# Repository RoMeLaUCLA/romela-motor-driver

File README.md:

# RoMeLa motor driver gen2
 Motor driver PCB and firmware designed for RoMeLa actuators. 
 
 Block diagram of the hardware:

 ## System Diagram

 # PCB reference

[Link to gen2 schematics](/pcb/rev1/schematics_Motor_Gen2.pdf)

[Link to gen2L schematics](/pcb/split/gen2L/schematics_Motor_Gen2L.pdf)

[Link to gen2P schematics](/pcb/split/gen2P/schematics_Motor_Gen2P.pdf)

# Change Log
12/1/2022 Ver. 581
- First version using gcc(STM32CubeIDE)

04/13/2022 Ver. 48D
- Added 0.5ms de-glitch time for E-Stop input and 1sec minimum E-Stop time.

02/09/2022 Ver. 449
- Fixed MCU lock up with RS-485 over run present in Ver. 2BB.

09/27/2021 Ver. 33B
- Random ABS Posi error and Init error on power-up.

05/27/2021 Ver. 2BB
- Fixed cogging torque comp. issue.

03/31/2021 Ver. 27F
- Limit Id Max changed to Limit Acc Max
- Limit Iq Max changed to Limit I Max
- Added external Estop signal (wiring change) and command
- Acceleration limited S curve added to Mode 2 (position mode).
- Goal velocity and Iq feedforward term enabled for Mode 3. (Allow Id, Iq, Velocity, Position reference all at once)

09/29/2020 Ver. 130-137
- Added support for KB01_R18 and KB01_R24. (External AS5047 Encoder)

06/23/2020 Ver. D7
- Fixed joint limit issue.

05/20/2020 Ver. B4
- GEN2 Initial release.

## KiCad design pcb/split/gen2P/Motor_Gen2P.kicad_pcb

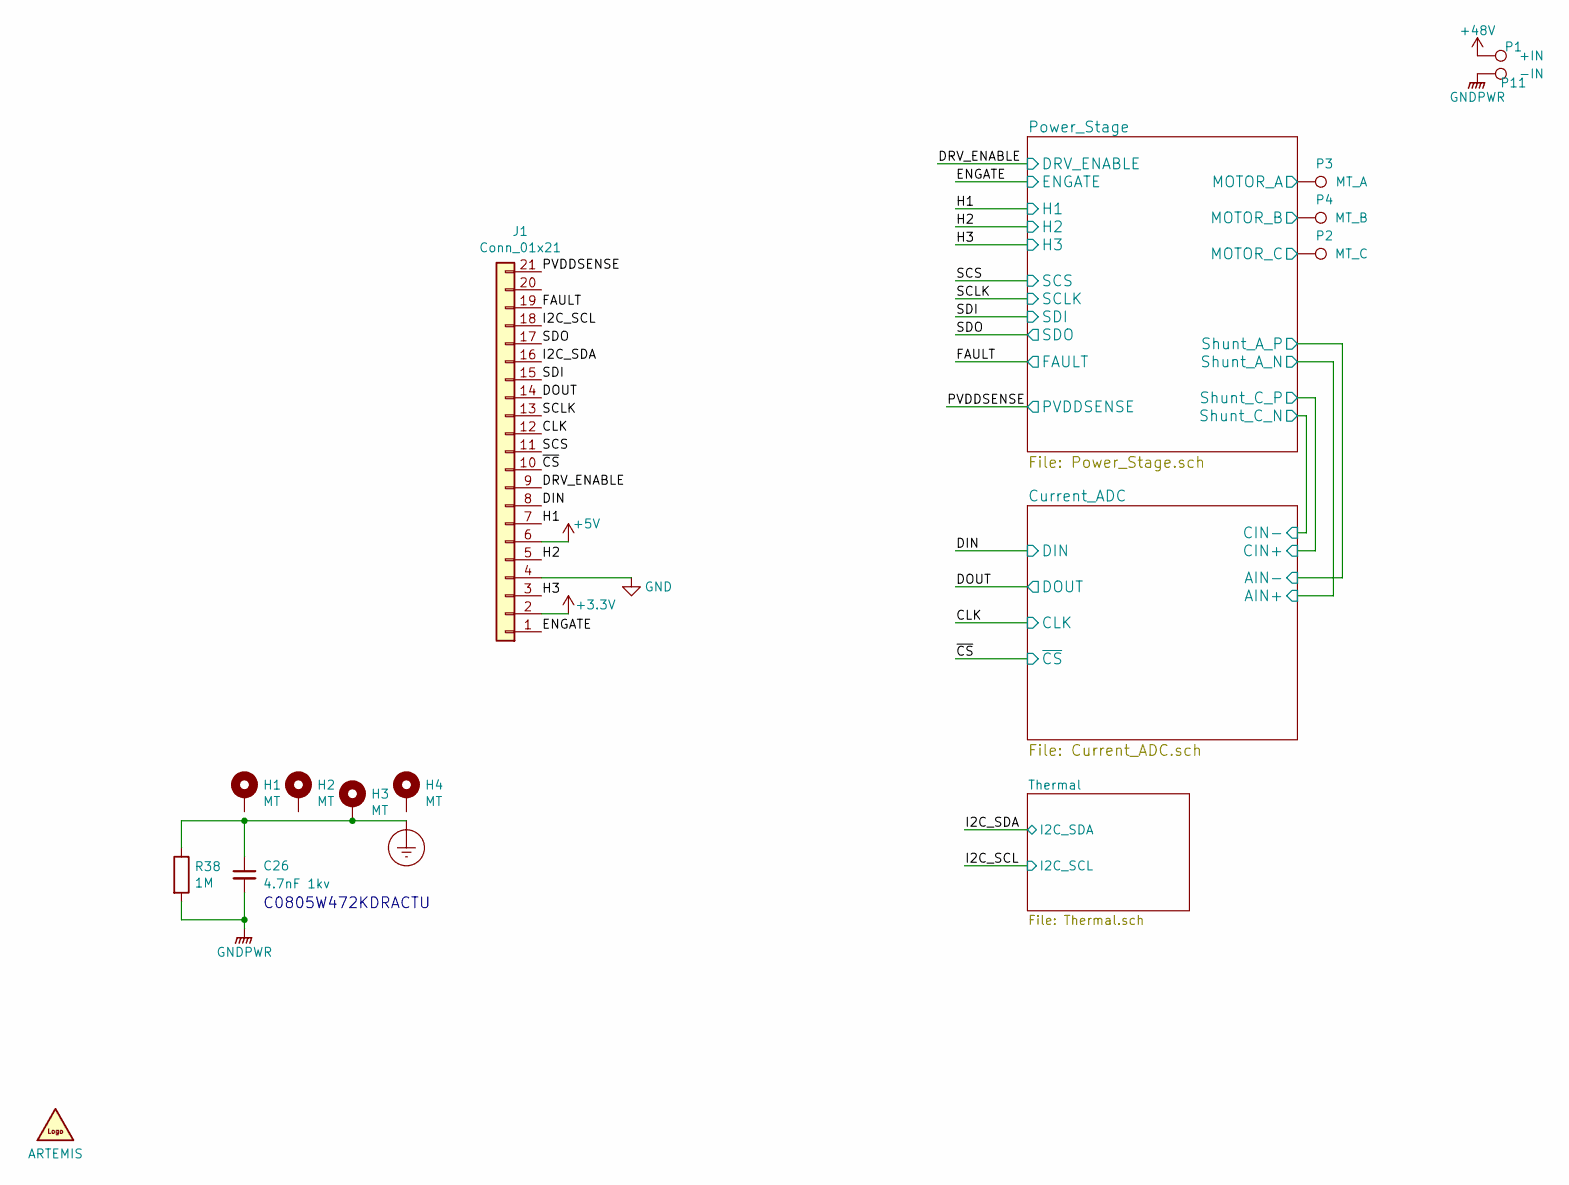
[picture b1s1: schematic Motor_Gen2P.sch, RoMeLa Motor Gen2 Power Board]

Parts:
C26: 4.7nF 1kv; C_0805_2012Metric
G1: ARTEMIS; artemis_logo_small
H1, H2, H3, H4: MT; MountingHole_2.7mm_M2.5_Pad_Via
J1: Conn_01x21; Molex_5019122190_2Rows-21Pins_P0.30mm
P1: +IN; Motor_winding_SMT
P2: MT_C; motor_winding_oval_3mm
P3: MT_A; motor_winding_oval_3mm
P4: MT_B; motor_winding_oval_3mm
P11: -IN; Motor_winding_SMT
R38: 1M; R_0805_2012Metric

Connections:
+3V3: J1.2; also elsewhere on the board
+5V: J1.6; also elsewhere on the board
+48V: P1.1; also elsewhere on the board
/CLK: J1.12; also elsewhere on the board
/DIN: J1.8; also elsewhere on the board
/DOUT: J1.14; also elsewhere on the board
/DRV_ENABLE: J1.9; also elsewhere on the board
/ENGATE: J1.1; also elsewhere on the board
/FAULT: J1.19; also elsewhere on the board
/H1: J1.7; also elsewhere on the board
/H2: J1.5; also elsewhere on the board
/H3: J1.3; also elsewhere on the board
/I2C_SCL: J1.18; also elsewhere on the board
/I2C_SDA: J1.16; also elsewhere on the board
/PVDDSENSE: J1.21; also elsewhere on the board
/Power_Stage/MOTOR_A: P3.1; also elsewhere on the board
/Power_Stage/MOTOR_B: P4.1; also elsewhere on the board
/Power_Stage/MOTOR_C: P2.1; also elsewhere on the board
/SCLK: J1.13; also elsewhere on the board
/SCS: J1.11; also elsewhere on the board
/SDI: J1.15; also elsewhere on the board
/SDO: J1.17; also elsewhere on the board
/~CS: J1.10; also elsewhere on the board
Earth_Protective: C26.1, H3.1, R38.1
GND: J1.4; also elsewhere on the board
GNDPWR: C26.2, P11.1, R38.2; also elsewhere on the board

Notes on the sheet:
C0805W472KDRACTU

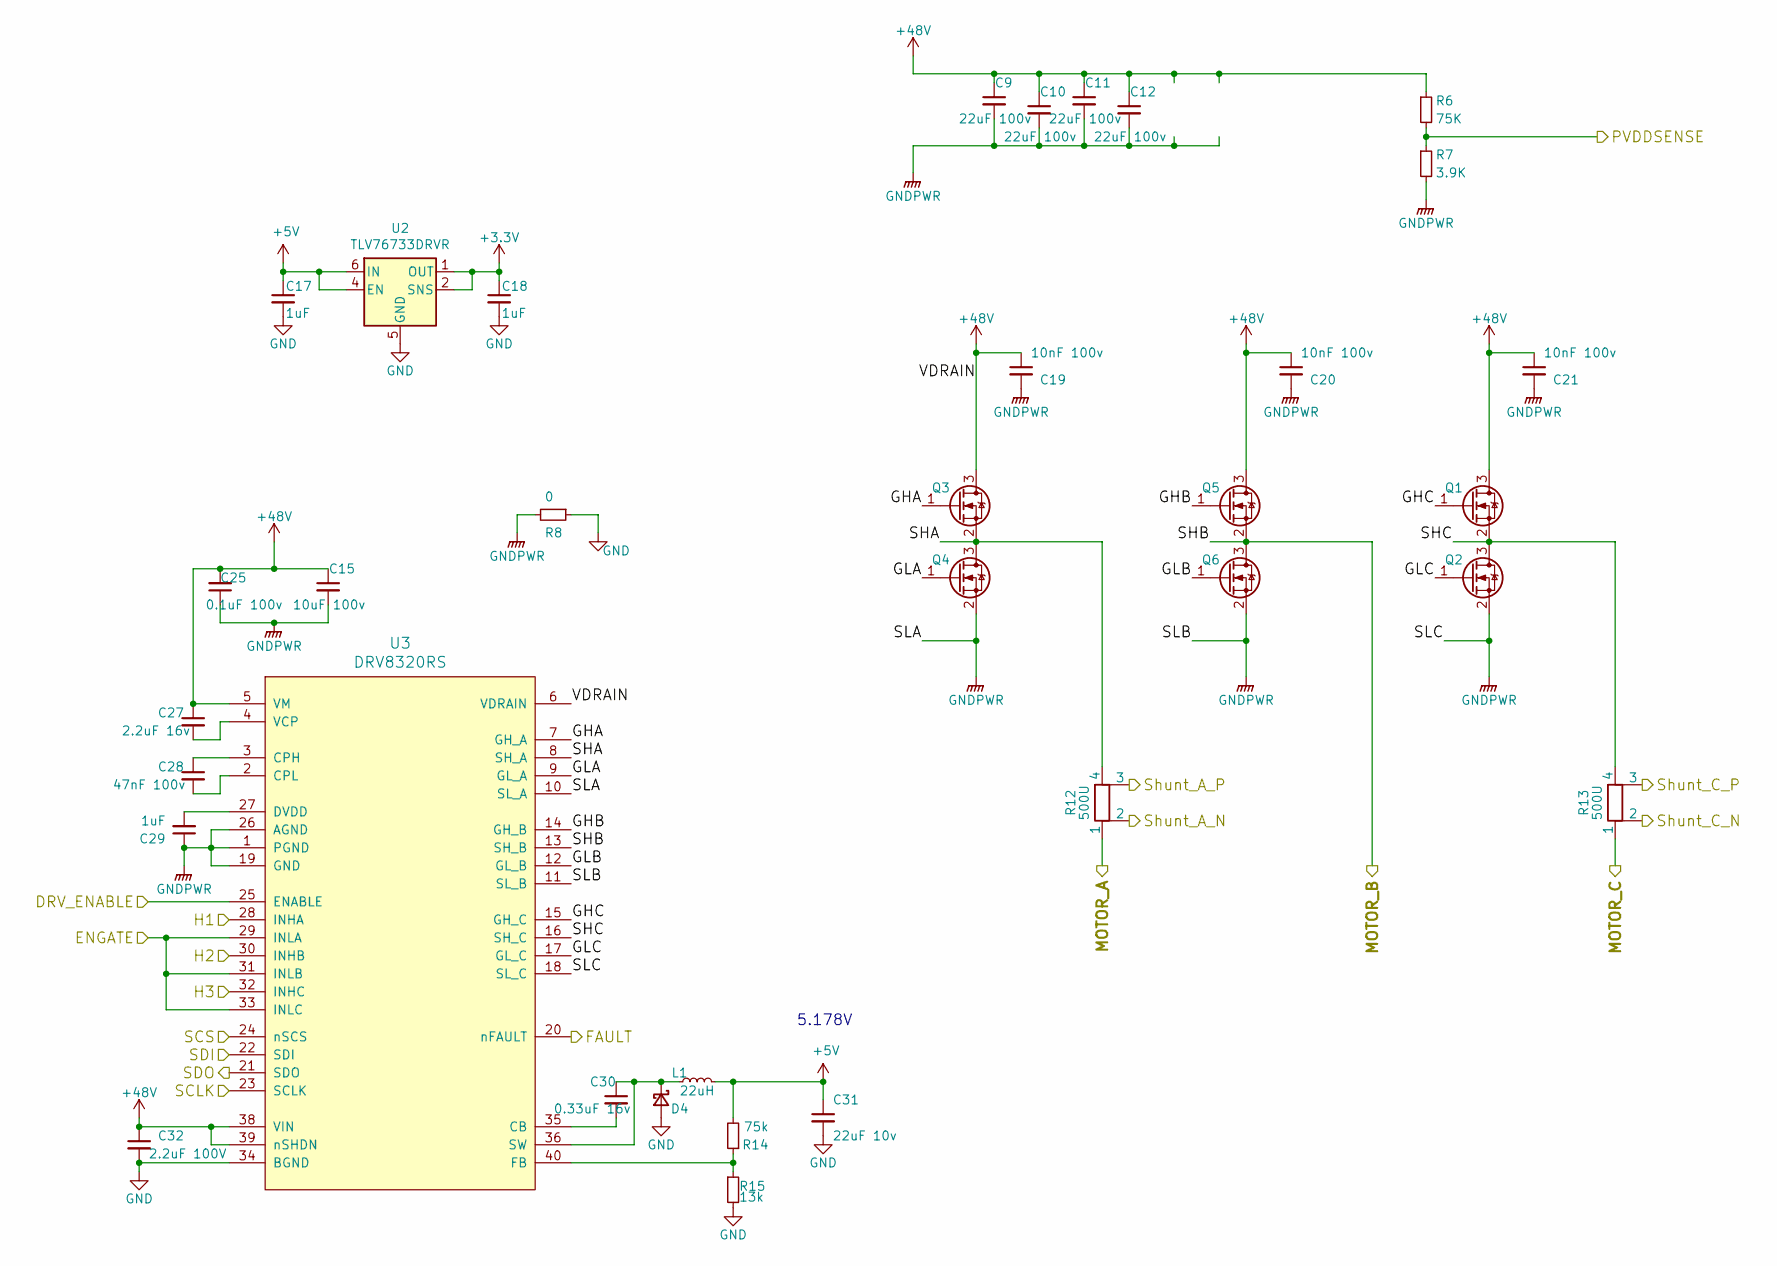
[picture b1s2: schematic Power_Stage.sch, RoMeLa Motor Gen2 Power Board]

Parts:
C9, C10, C11, C12: 22uF 100v; C_2220_5650Metric
C15: 10uF 100v; C_1210_3225Metric
C17, C18, C29: 1uF; C_0603_1608Metric
C19, C20, C21: 10nF 100v; C_0603_1608Metric
C25: 0.1uF 100v; C_0603_1608Metric
C27: 2.2uF 16v; C_0603_1608Metric
C28: 47nF 100v; C_0603_1608Metric
C30: 0.33uF 16v; C_0603_1608Metric
C31: 22uF 10v; C_1206_3216Metric
C32: 2.2uF 100V; C_1206_3216Metric
D4: D_Schottky_Small; D_TUMD2
L1: 22uH; L_Taiyo-Yuden_DND4040WK
Q1, Q2, Q3, Q4, Q5, Q6: NMOS; DFNW8_8.3x8.4_short
R6: 75K; R_0402_1005Metric
R7: 3.9K; R_0402_1005Metric
R8: 0; NetTie-2_SMD_Pad0.5mm
R12, R13: 500U; RES_W1612_4Terminal
R14: 75k; R_0402_1005Metric
R15: 13k; R_0402_1005Metric
U2: TLV76733DRVR; WSON-6-1EP_2x2mm_P0.65mm_EP1x1.6mm
U3: DRV8320RS; Texas_S-PVQFN-N40_EP4.15x4.15mm

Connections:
+3V3: C18.1, U2.1 (OUT), U2.2 (SNS); also elsewhere on the board
+5V: C17.1, C31.1, L1.2, R14.2, U2.4 (EN), U2.6 (IN); also elsewhere on the board
+48V: C9.1, C10.1, C11.1, C12.1, C15.1, C19.1, C20.1, C21.1, C25.2, C27.1, C32.1, Q1.3 (D), Q3.3 (D), Q5.3 (D), R6.1, U3.5 (VM), U3.6 (VDRAIN), U3.38 (VIN), U3.39 (nSHDN); also elsewhere on the board
/Current_ADC/AIN+: R12.2; also elsewhere on the board
/Current_ADC/AIN-: R12.3; also elsewhere on the board
/Current_ADC/CIN+: R13.3; also elsewhere on the board
/Current_ADC/CIN-: R13.2; also elsewhere on the board
/DRV_ENABLE: U3.25 (ENABLE); also elsewhere on the board
/ENGATE: U3.29 (INLA), U3.31 (INLB), U3.33 (INLC); also elsewhere on the board
/FAULT: U3.20 (nFAULT); also elsewhere on the board
/H1: U3.28 (INHA); also elsewhere on the board
/H2: U3.30 (INHB); also elsewhere on the board
/H3: U3.32 (INHC); also elsewhere on the board
/PVDDSENSE: R6.2, R7.1; also elsewhere on the board
/Power_Stage/GHA: Q3.1 (G), U3.7 (GH_A)
/Power_Stage/GHB: Q5.1 (G), U3.14 (GH_B)
/Power_Stage/GHC: Q1.1 (G), U3.15 (GH_C)
/Power_Stage/GLA: Q4.1 (G), U3.9 (GL_A)
/Power_Stage/GLB: Q6.1 (G), U3.12 (GL_B)
/Power_Stage/GLC: Q2.1 (G), U3.17 (GL_C)
/Power_Stage/MOTOR_A: R12.1; also elsewhere on the board
/Power_Stage/MOTOR_B: Q5.2 (S), Q6.3 (D), U3.13 (SH_B); also elsewhere on the board
/Power_Stage/MOTOR_C: R13.1; also elsewhere on the board
/Power_Stage/SHA: Q3.2 (S), Q4.3 (D), R12.4, U3.8 (SH_A)
/Power_Stage/SHC: Q1.2 (S), Q2.3 (D), R13.4, U3.16 (SH_C)
/SCLK: U3.23 (SCLK); also elsewhere on the board
/SCS: U3.24 (nSCS); also elsewhere on the board
/SDI: U3.22 (SDI); also elsewhere on the board
/SDO: U3.21 (SDO); also elsewhere on the board
GND: C17.2, C18.2, C31.2, C32.2, D4.2 (A), R8.1, R15.2, U2.3 (GND), U2.5 (GND), U2.7 (GND), U3.34 (BGND); also elsewhere on the board
GNDPWR: C9.2, C10.2, C11.2, C12.2, C15.2, C19.2, C20.2, C21.2, C25.1, C29.1, Q2.2 (S), Q4.2 (S), Q6.2 (S), R7.2, R8.2, U3.1 (PGND), U3.10 (SL_A), U3.11 (SL_B), U3.18 (SL_C), U3.19 (GND), U3.26 (AGND), U3.41 (PAD); also elsewhere on the board
unnamed: C27.2, U3.4 (VCP)
unnamed: C28.1, U3.3 (CPH)
unnamed: C28.2, U3.2 (CPL)
unnamed: C29.2, U3.27 (DVDD)
unnamed: C30.1, D4.1 (K), L1.1, U3.36 (SW)
unnamed: C30.2, U3.35 (CB)
unnamed: R14.1, R15.1, U3.40 (FB)

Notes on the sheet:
5.178V

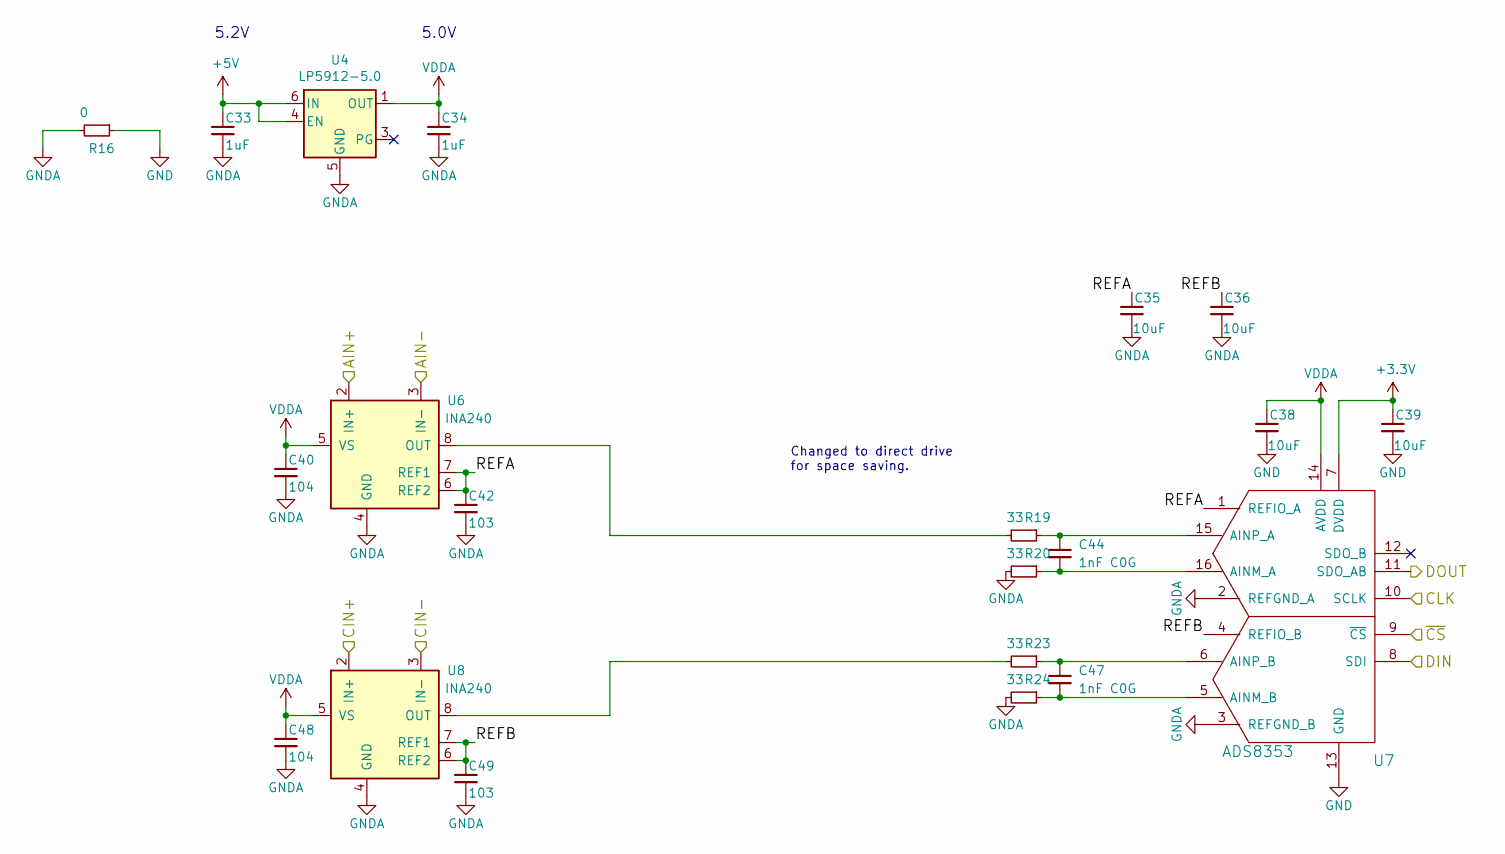
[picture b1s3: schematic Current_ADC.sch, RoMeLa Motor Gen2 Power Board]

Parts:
C33, C34: 1uF; C_0603_1608Metric
C35, C36, C38, C39: 10uF; C_0805_2012Metric
C40, C48: 104; C_0402_1005Metric
C42, C49: 103; C_0402_1005Metric
C44, C47: 1nF C0G; C_0402_1005Metric
R16: 0; NetTie-2_SMD_Pad0.5mm
R19, R20, R23, R24: 33; R_0402_1005Metric
U4: LP5912-5.0; WSON-6-1EP_2x2mm_P0.65mm_EP1x1.6mm
U6, U8: INA240; TSSOP-8_4.4x3mm_P0.65mm
U7: ADS8353; WQFN-16-1EP_3x3mm_P0.5mm_EP0.8x0.8mm

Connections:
+3V3: C39.1, U7.7 (DVDD); also elsewhere on the board
+5V: C33.1, U4.4 (EN), U4.6 (IN); also elsewhere on the board
/CLK: U7.10 (SCLK); also elsewhere on the board
/Current_ADC/AIN+: U6.2 (IN+); also elsewhere on the board
/Current_ADC/AIN-: U6.3 (IN-); also elsewhere on the board
/Current_ADC/CIN+: U8.2 (IN+); also elsewhere on the board
/Current_ADC/CIN-: U8.3 (IN-); also elsewhere on the board
/Current_ADC/REFA: C35.1, C42.1, U6.6 (REF2), U6.7 (REF1), U7.1 (REFIO_A)
/Current_ADC/REFB: C36.1, C49.1, U7.4 (REFIO_B), U8.6 (REF2), U8.7 (REF1)
/DIN: U7.8 (SDI); also elsewhere on the board
/DOUT: U7.11 (SDO_AB); also elsewhere on the board
/~CS: U7.9 (~CS); also elsewhere on the board
GND: C38.2, C39.2, R16.1, U7.13 (GND), U7.17 (Pad); also elsewhere on the board
GNDA: C33.2, C34.2, C35.2, C36.2, C40.2, C42.2, C48.2, C49.2, R16.2, R20.2, R24.2, U4.5 (GND), U4.7 (GND), U6.4 (GND), U7.2 (REFGND_A), U7.3 (REFGND_B), U8.4 (GND)
unnamed: C44.1, R19.1, U7.15 (AINP_A)
unnamed: C44.2, R20.1, U7.16 (AINM_A)
unnamed: C47.1, R23.1, U7.6 (AINP_B)
unnamed: C47.2, R24.1, U7.5 (AINM_B)
unnamed: R19.2, U6.8 (OUT)
unnamed: R23.2, U8.8 (OUT)
VDDA: C34.1, C38.1, C40.1, C48.1, U4.1 (OUT), U6.5 (VS), U7.14 (AVDD), U8.5 (VS)

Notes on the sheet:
5.2V
5.0V
Changed to direct drive for space saving.

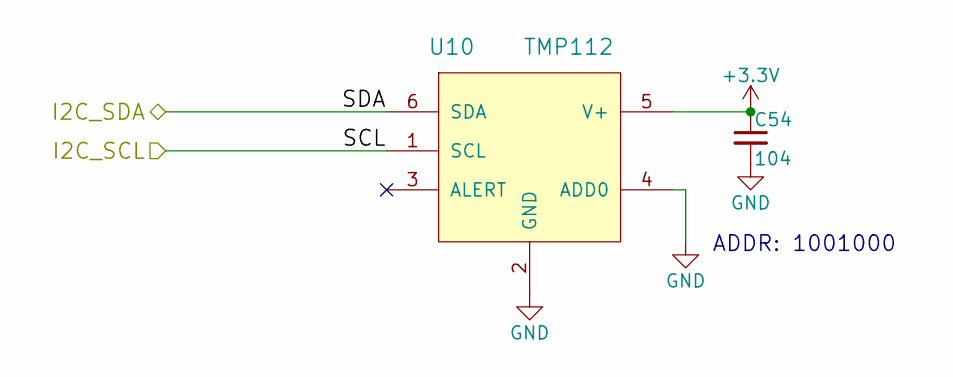
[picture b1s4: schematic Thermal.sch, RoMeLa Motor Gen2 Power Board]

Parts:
C54: 104; C_0402_1005Metric
U10: TMP112; SOT-563

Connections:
+3V3: C54.1, U10.5 (V+); also elsewhere on the board
/I2C_SCL: U10.1 (SCL); also elsewhere on the board
/I2C_SDA: U10.6 (SDA); also elsewhere on the board
GND: C54.2, U10.2 (GND), U10.4 (ADD0); also elsewhere on the board

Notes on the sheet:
ADDR: 1001000

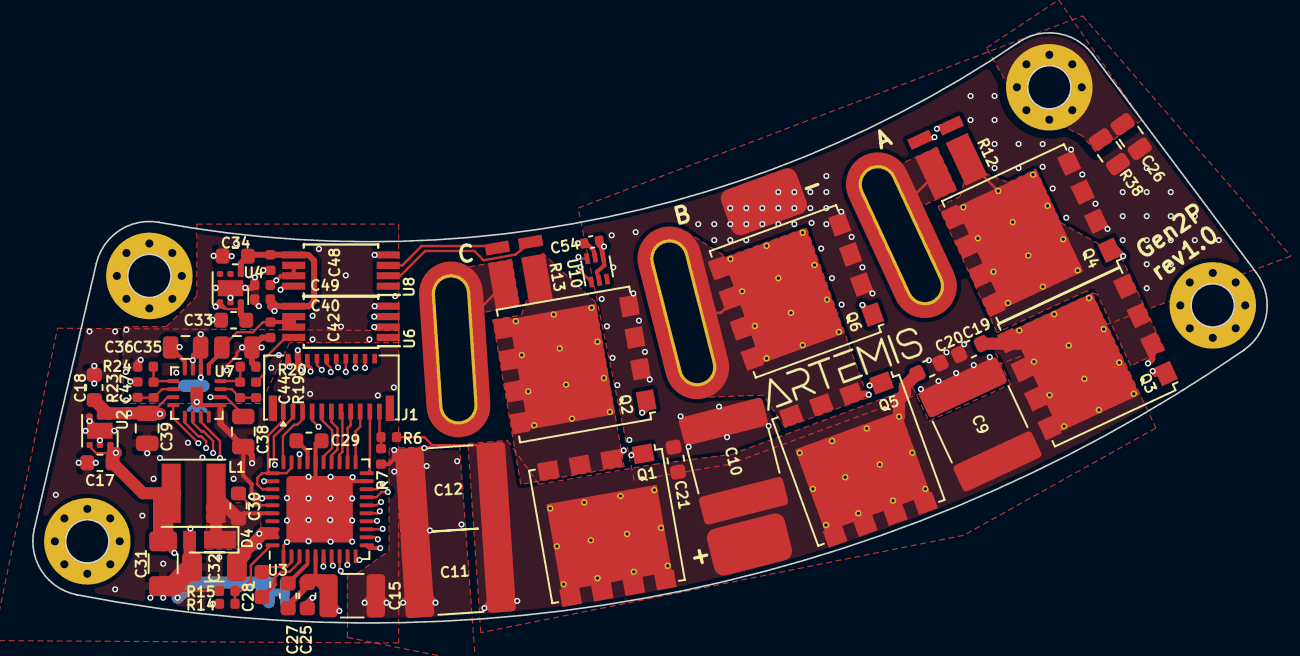
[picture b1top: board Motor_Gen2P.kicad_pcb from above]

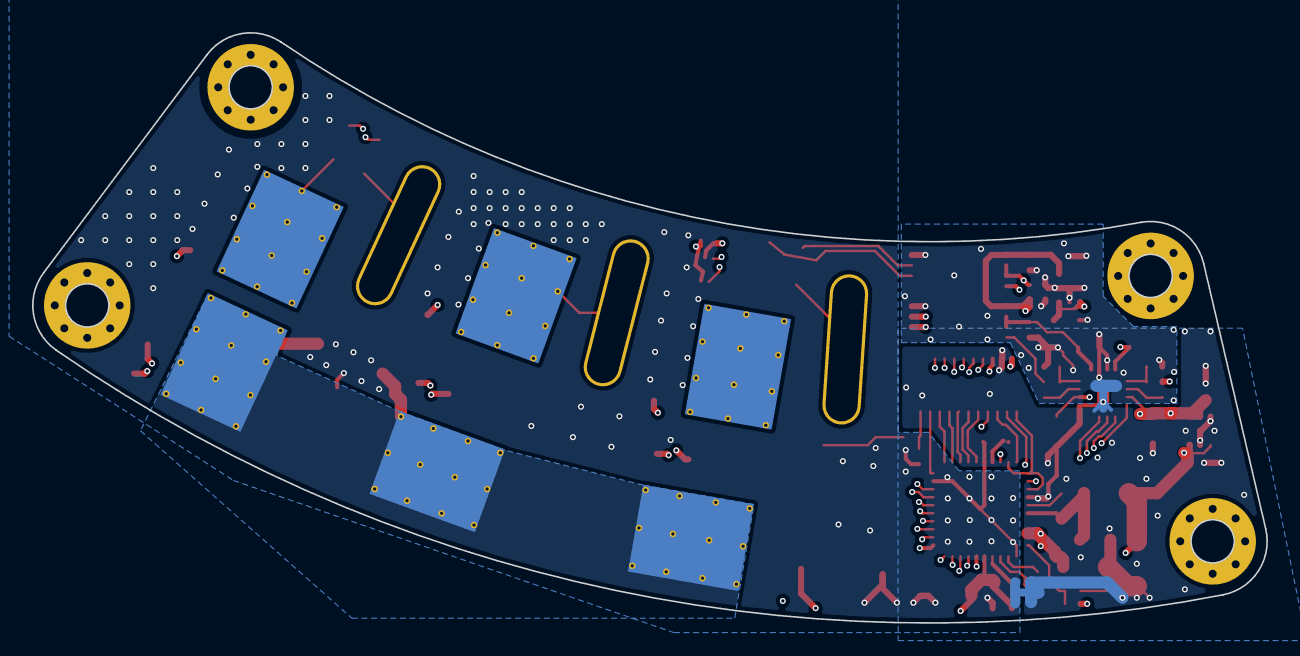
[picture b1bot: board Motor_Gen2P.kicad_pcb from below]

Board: 4 copper layers, 77.1 x 36.8 mm, 70 parts (2 on the bottom side), 55 nets.

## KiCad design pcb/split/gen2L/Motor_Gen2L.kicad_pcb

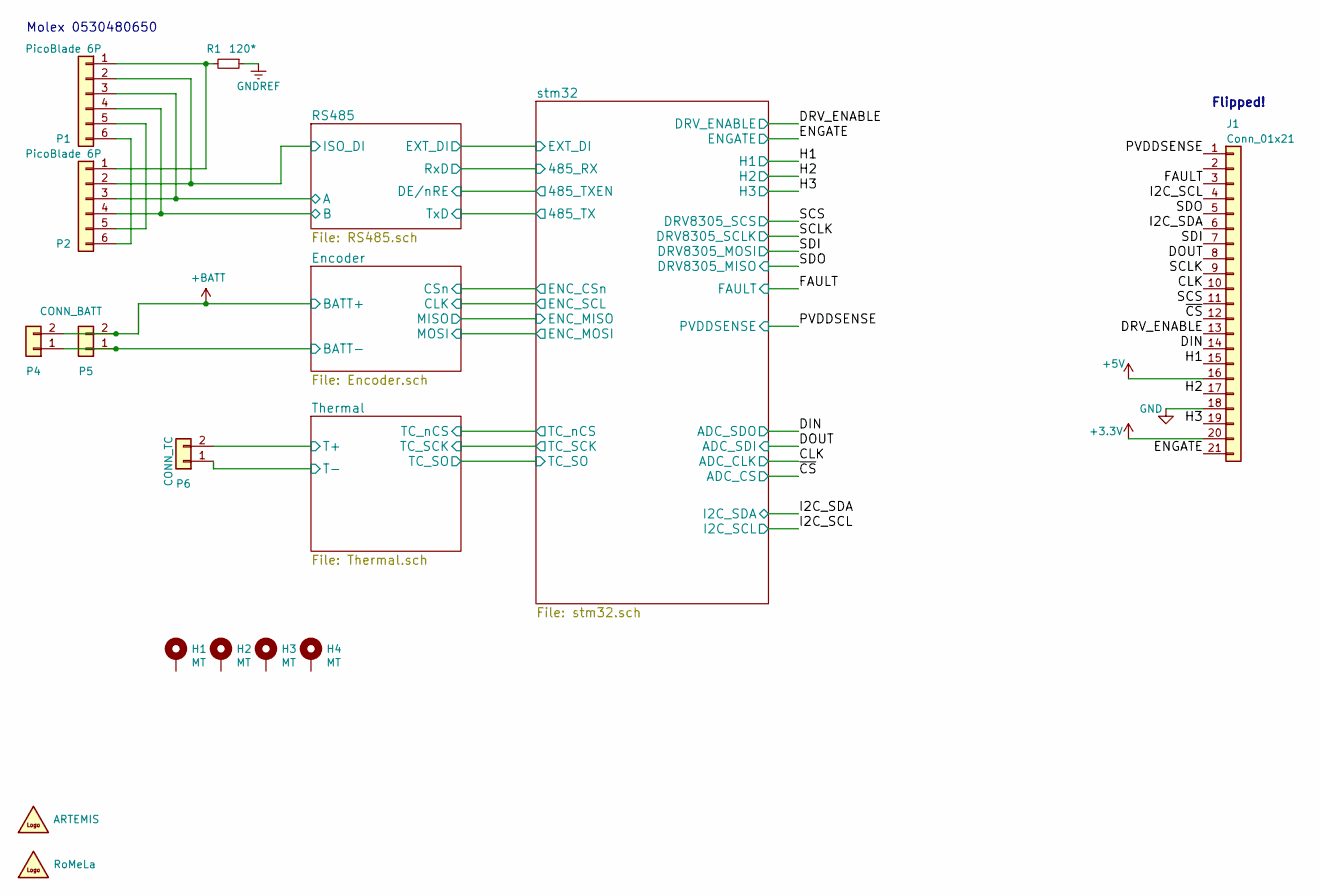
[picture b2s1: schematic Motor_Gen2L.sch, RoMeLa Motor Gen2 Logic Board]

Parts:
G1: ARTEMIS; artemis_logo_small
G2: RoMeLa; LOGO
H1, H2, H3, H4: MT; MountingHole_2.7mm_M2.5_Pad_Via
J1: Conn_01x21; Molex_5019122190_2Rows-21Pins_P0.30mm
P1, P2: PicoBlade 6P; Molex_PicoBlade_53048-0650_1x06_P1.25mm_Horizontal
P4, P5: CONN_BATT; Molex_PicoBlade_53048-0210_1x02_P1.25mm_Horizontal
P6: CONN_TC; JST_SH_SM02B-SRSS-TB_1x02-1MP_P1.00mm_Horizontal
R1: 120*; R_0603_1608Metric

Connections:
+3V3: J1.20; also elsewhere on the board
+5V: J1.16; also elsewhere on the board
+BATT: P4.2, P5.2; also elsewhere on the board
/CLK: J1.10; also elsewhere on the board
/DIN: J1.14; also elsewhere on the board
/DOUT: J1.8; also elsewhere on the board
/DRV_ENABLE: J1.13; also elsewhere on the board
/ENGATE: J1.21; also elsewhere on the board
/FAULT: J1.3; also elsewhere on the board
/H1: J1.15; also elsewhere on the board
/H2: J1.17; also elsewhere on the board
/H3: J1.19; also elsewhere on the board
/I2C_SCL: J1.4; also elsewhere on the board
/I2C_SDA: J1.6; also elsewhere on the board
/PVDDSENSE: J1.1; also elsewhere on the board
/RS485/A: P1.3, P2.3; also elsewhere on the board
/RS485/B: P1.4, P2.4; also elsewhere on the board
/RS485/ISO_DI: P1.2, P2.2; also elsewhere on the board
/SCLK: J1.9; also elsewhere on the board
/SCS: J1.11; also elsewhere on the board
/SDI: J1.7; also elsewhere on the board
/SDO: J1.5; also elsewhere on the board
/Thermal/T+: P6.2; also elsewhere on the board
/Thermal/T-: P6.1; also elsewhere on the board
/~CS: J1.12; also elsewhere on the board
GND: J1.18, P4.1, P5.1; also elsewhere on the board
GNDREF: R1.1; also elsewhere on the board
unnamed: P1.1, P2.1, R1.2
unnamed: P1.5, P2.5
unnamed: P1.6, P2.6

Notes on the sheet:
Molex 0530480650
Flipped!

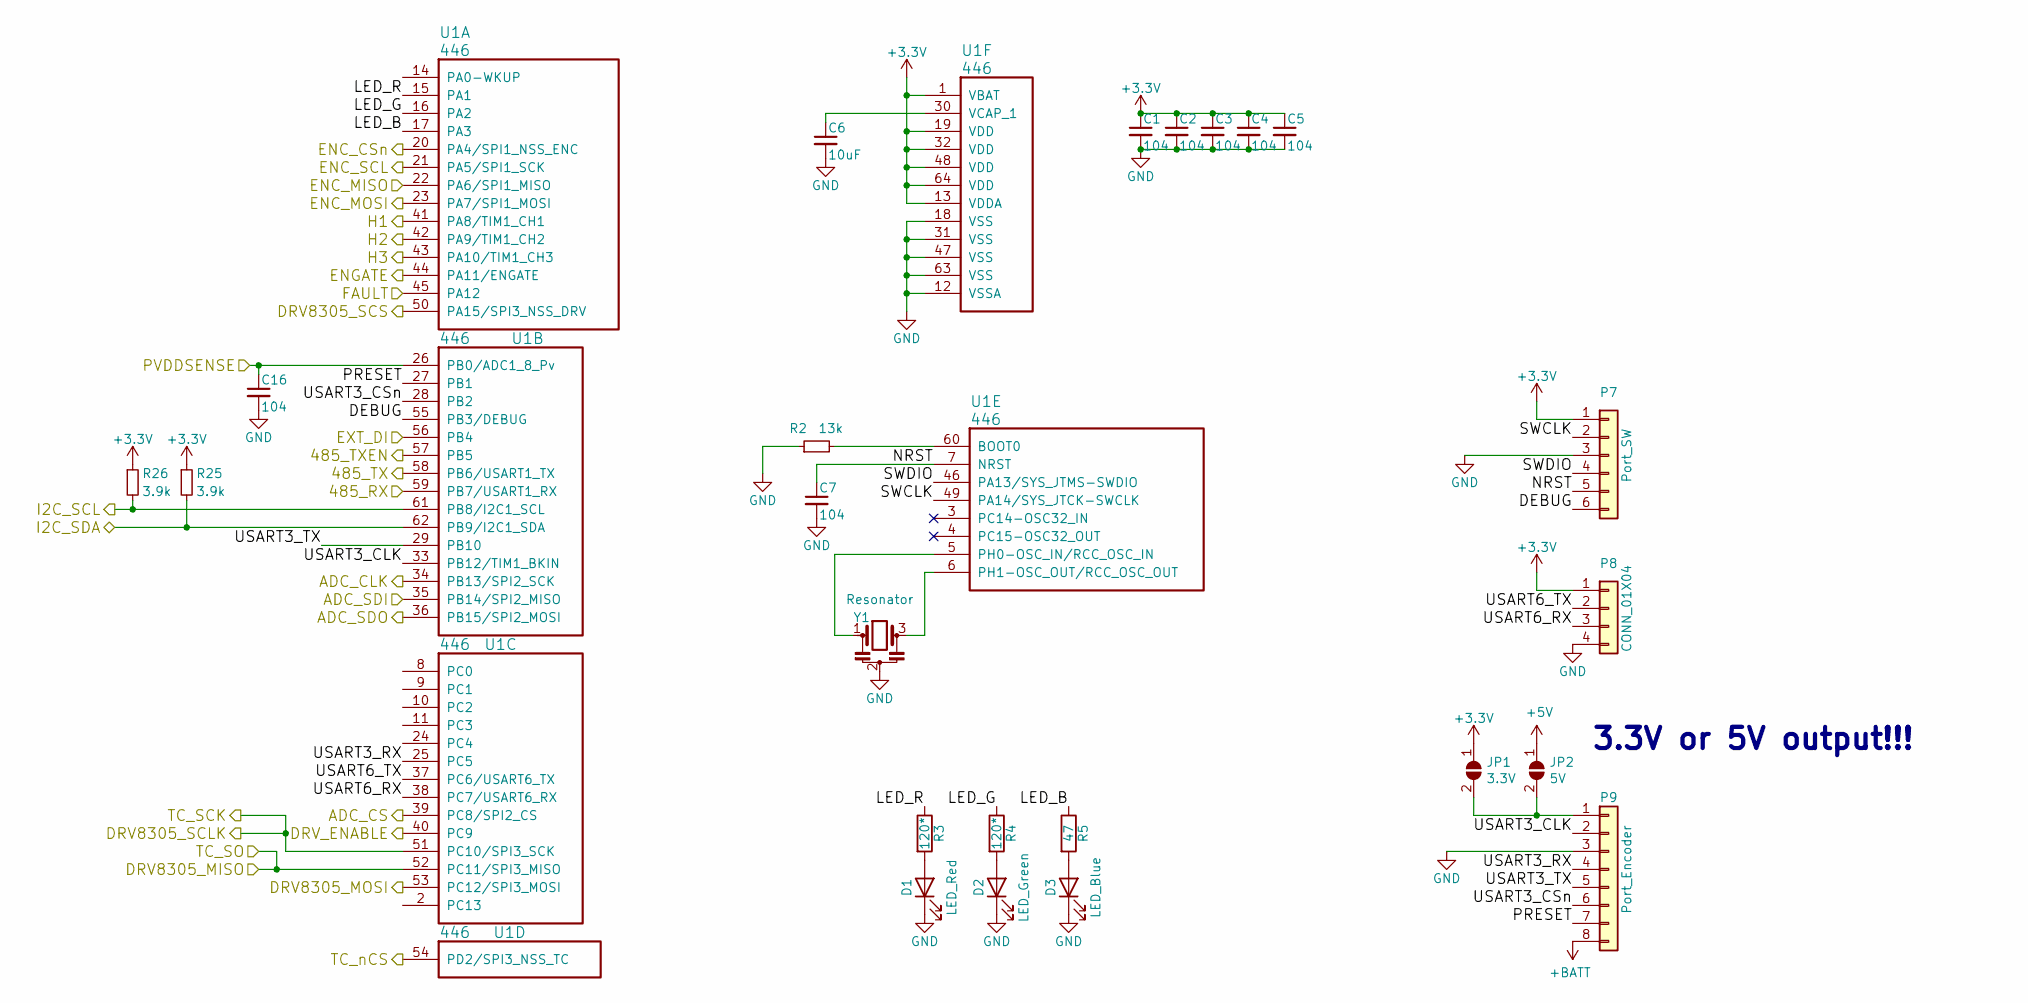
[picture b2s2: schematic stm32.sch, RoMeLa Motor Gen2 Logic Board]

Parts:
C1, C2, C3, C4, C5, C7, C16: 104; C_0402_1005Metric
C6: 10uF; C_0805_2012Metric
D1: LED_Red; LED_0603_1608Metric
D2: LED_Green; LED_0603_1608Metric
D3: LED_Blue; LED_0603_1608Metric
JP1: 3.3V; SolderJumper_Open_TrianglePad
JP2: 5V; SolderJumper_Open_TrianglePad
P7: Port_SW; JST_SH_BM06B-SRSS-TB_1x06-1MP_P1.00mm_Vertical
P8: CONN_01X04; JST_SH_BM04B-SRSS-TB_1x04-1MP_P1.00mm_Vertical
P9: Port_Encoder; FFC_8POS_0.5mm_BackFlip
R2: 13k; R_0402_1005Metric
R3, R4: 120*; R_0603_1608Metric
R5: 47; R_0603_1608Metric
R25, R26: 3.9k; R_0402_1005Metric
U1: 446; LQFP-64_10x10mm_P0.5mm
Y1: Resonator; Resonator_3.2x1.3

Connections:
+3V3: C1.1, C2.1, C3.1, C4.1, C5.1, JP1.1 (A), P7.1, P8.1, R25.1, R26.1, U1.1 (VBAT), U1.13 (VDDA), U1.19 (VDD), U1.32 (VDD), U1.48 (VDD), U1.64 (VDD); also elsewhere on the board
+5V: JP2.1 (A); also elsewhere on the board
+BATT: P9.8; also elsewhere on the board
/CLK: U1.34 (PB13/SPI2_SCK); also elsewhere on the board
/DIN: U1.36 (PB15/SPI2_MOSI); also elsewhere on the board
/DOUT: U1.35 (PB14/SPI2_MISO); also elsewhere on the board
/DRV_ENABLE: U1.40 (PC9); also elsewhere on the board
/ENGATE: U1.44 (PA11/ENGATE); also elsewhere on the board
/Encoder/CLK: U1.21 (PA5/SPI1_SCK); also elsewhere on the board
/Encoder/CSn: U1.20 (PA4/SPI1_NSS_ENC); also elsewhere on the board
/FAULT: U1.45 (PA12); also elsewhere on the board
/H1: U1.41 (PA8/TIM1_CH1); also elsewhere on the board
/H2: U1.42 (PA9/TIM1_CH2); also elsewhere on the board
/H3: U1.43 (PA10/TIM1_CH3); also elsewhere on the board
/I2C_SCL: R26.2, U1.61 (PB8/I2C1_SCL); also elsewhere on the board
/I2C_SDA: R25.2, U1.62 (PB9/I2C1_SDA); also elsewhere on the board
/PVDDSENSE: C16.1, U1.26 (PB0/ADC1_8_Pv); also elsewhere on the board
/RS485/EXT_DI: U1.56 (PB4); also elsewhere on the board
/SCLK: U1.51 (PC10/SPI3_SCK); also elsewhere on the board
/SCS: U1.50 (PA15/SPI3_NSS_DRV); also elsewhere on the board
/SDI: U1.53 (PC12/SPI3_MOSI); also elsewhere on the board
/SDO: U1.52 (PC11/SPI3_MISO); also elsewhere on the board
/Thermal/TC_nCS: U1.54 (PD2/SPI3_NSS_TC); also elsewhere on the board
/stm32/485_RX: U1.59 (PB7/USART1_RX); also elsewhere on the board
/stm32/485_TX: U1.58 (PB6/USART1_TX); also elsewhere on the board
/stm32/485_TXEN: U1.57 (PB5); also elsewhere on the board
/stm32/DEBUG: P7.6, U1.55 (PB3/DEBUG)
/stm32/ENC_MISO: U1.22 (PA6/SPI1_MISO); also elsewhere on the board
/stm32/ENC_MOSI: U1.23 (PA7/SPI1_MOSI); also elsewhere on the board
/stm32/LED_B: R5.1, U1.17 (PA3)
/stm32/LED_G: R4.1, U1.16 (PA2)
/stm32/LED_R: R3.1, U1.15 (PA1)
/stm32/NRST: C7.1, P7.5, U1.7 (NRST)
/stm32/PRESET: P9.7, U1.27 (PB1)
/stm32/SWCLK: P7.2, U1.49 (PA14/SYS_JTCK-SWCLK)
/stm32/SWDIO: P7.4, U1.46 (PA13/SYS_JTMS-SWDIO)
/stm32/USART3_CLK: P9.2, U1.33 (PB12/TIM1_BKIN)
/stm32/USART3_CSn: P9.6, U1.28 (PB2)
/stm32/USART3_RX: P9.4, U1.25 (PC5)
/stm32/USART3_TX: P9.5, U1.29 (PB10)
/stm32/USART6_RX: P8.3, U1.38 (PC7/USART6_RX)
/stm32/USART6_TX: P8.2, U1.37 (PC6/USART6_TX)
/~CS: U1.39 (PC8/SPI2_CS); also elsewhere on the board
GND: C1.2, C2.2, C3.2, C4.2, C5.2, C6.2, C7.2, C16.2, D1.1 (K), D2.1 (K), D3.1 (K), P7.3, P8.4, P9.3, R2.1, U1.12 (VSSA), U1.18 (VSS), U1.31 (VSS), U1.47 (VSS), U1.63 (VSS), Y1.2; also elsewhere on the board
unnamed: C6.1, U1.30 (VCAP_1)
unnamed: D1.2 (A), R3.2
unnamed: D2.2 (A), R4.2
unnamed: D3.2 (A), R5.2
unnamed: JP1.2 (B), JP2.2 (B), P9.1
unnamed: R2.2, U1.60 (BOOT0)
unnamed: U1.5 (PH0-OSC_IN/RCC_OSC_IN), Y1.1
unnamed: U1.6 (PH1-OSC_OUT/RCC_OSC_OUT), Y1.3

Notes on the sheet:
3.3V or 5V output!!!

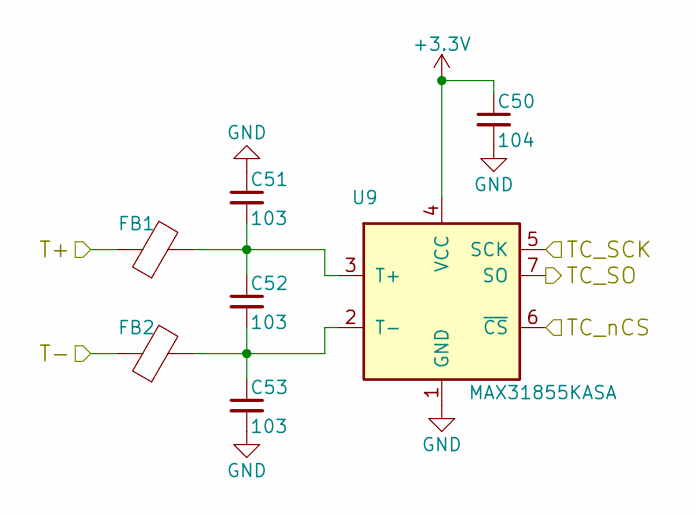
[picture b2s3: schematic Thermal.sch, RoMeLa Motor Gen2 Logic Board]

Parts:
C50: 104; C_0402_1005Metric
C51, C52, C53: 103; C_0402_1005Metric
FB1, FB2: Ferrite_Bead; R_0402_1005Metric
U9: MAX31855KASA; SOIC-8_3.9x4.9mm_P1.27mm

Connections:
+3V3: C50.1, U9.4 (VCC); also elsewhere on the board
/SCLK: U9.5 (SCK); also elsewhere on the board
/SDO: U9.7 (SO); also elsewhere on the board
/Thermal/T+: FB1.1; also elsewhere on the board
/Thermal/T-: FB2.1; also elsewhere on the board
/Thermal/TC_nCS: U9.6 (~CS~); also elsewhere on the board
GND: C50.2, C51.1, C53.2, U9.1 (GND); also elsewhere on the board
unnamed: C51.2, C52.1, FB1.2, U9.3 (T+)
unnamed: C52.2, C53.1, FB2.2, U9.2 (T-)

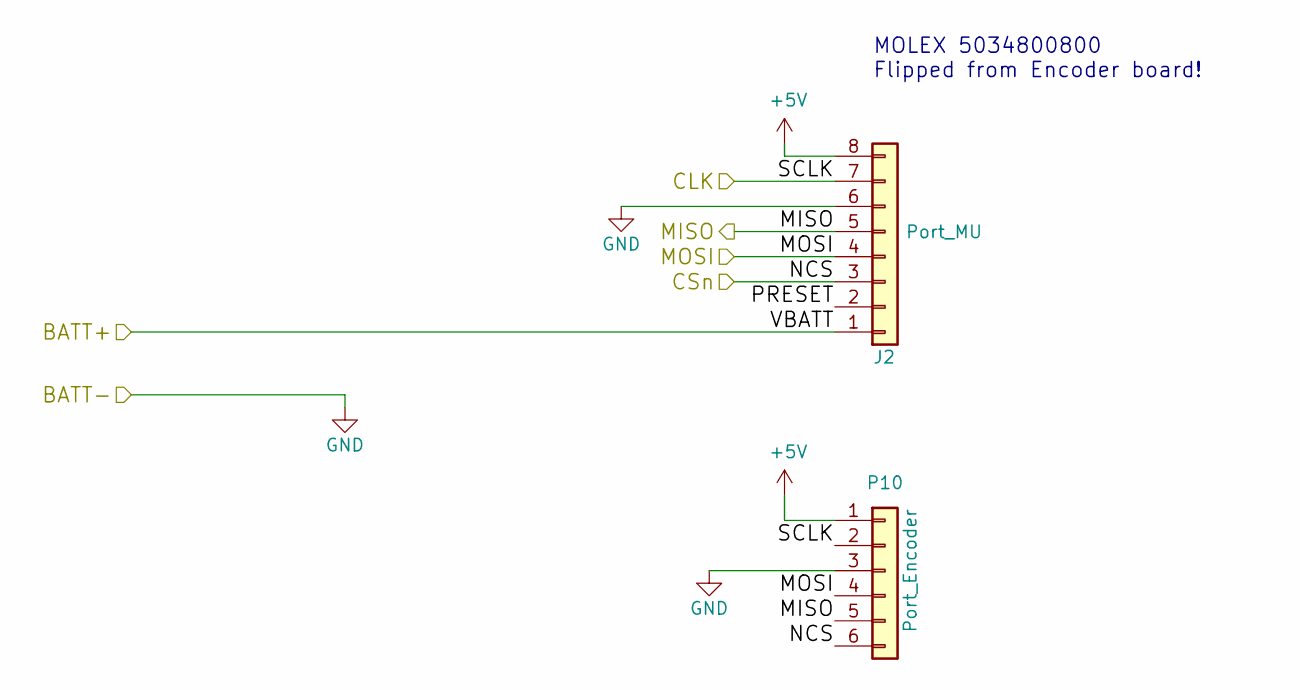
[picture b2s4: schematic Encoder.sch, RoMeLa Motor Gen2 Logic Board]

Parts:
J2: Port_MU; FFC_8POS_0.5mm_BackFlip
P10: Port_Encoder; JST_SH_BM06B-SRSS-TB_1x06-1MP_P1.00mm_Vertical

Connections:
+5V: J2.8, P10.1; also elsewhere on the board
+BATT: J2.1; also elsewhere on the board
/Encoder/CLK: J2.7, P10.2; also elsewhere on the board
/Encoder/CSn: J2.3, P10.6; also elsewhere on the board
/Encoder/PRESET: J2.2
/stm32/ENC_MISO: J2.5, P10.5; also elsewhere on the board
/stm32/ENC_MOSI: J2.4, P10.4; also elsewhere on the board
GND: J2.6, P10.3; also elsewhere on the board

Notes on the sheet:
MOLEX 5034800800 Flipped from Encoder board!

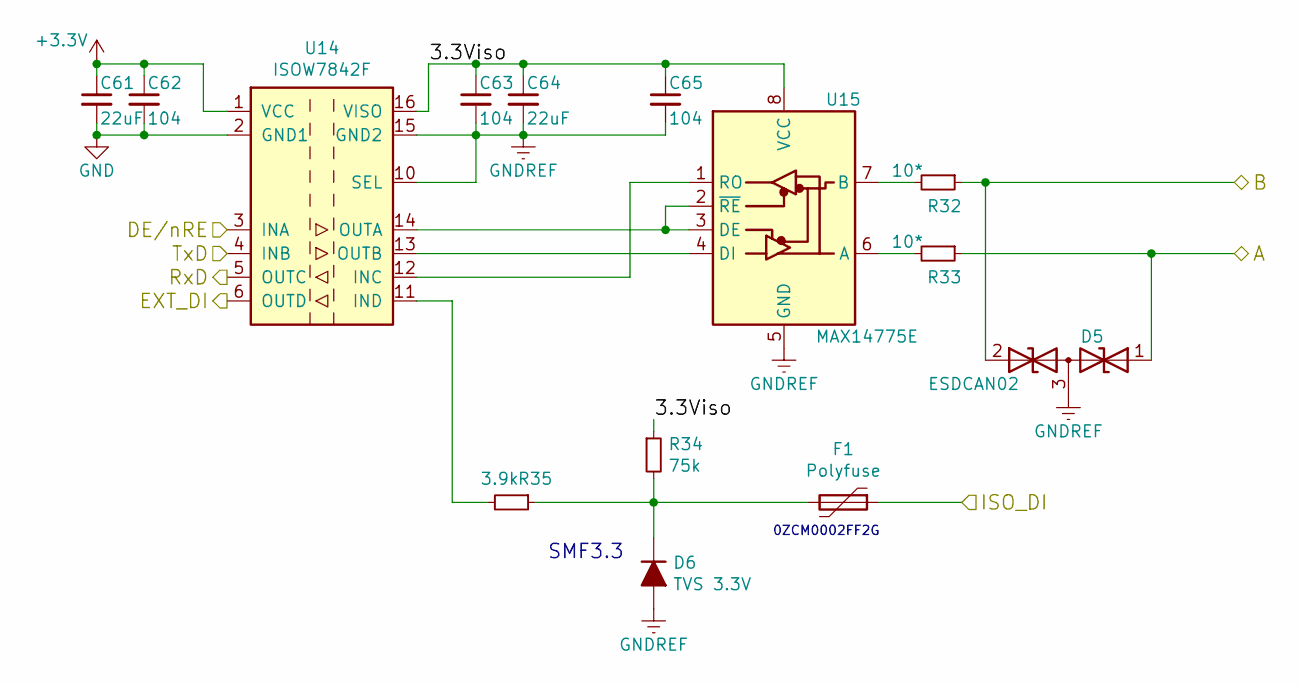
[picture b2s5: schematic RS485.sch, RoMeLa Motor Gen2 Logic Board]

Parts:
C61, C64: 22uF; C_1206_3216Metric
C62, C63, C65: 104; C_0402_1005Metric
D5: ESDCAN02; SOT-323_SC-70
D6: TVS 3.3V; D_SOD-123F
F1: Polyfuse; R_0603_1608Metric
R32, R33: 10*; R_0603_1608Metric
R34: 75k; R_0402_1005Metric
R35: 3.9k; R_0402_1005Metric
U14: ISOW7842F; SOIC-16W_7.5x10.3mm_P1.27mm
U15: MAX14775E; SOIC-8_3.9x4.9mm_P1.27mm

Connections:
+3V3: C61.1, C62.1, U14.1 (VCC); also elsewhere on the board
/RS485/3.3Viso: C63.1, C64.1, C65.1, R34.1, U14.16 (VISO), U15.8 (VCC)
/RS485/A: D5.1 (A1), R33.1; also elsewhere on the board
/RS485/B: D5.2 (A2), R32.1; also elsewhere on the board
/RS485/EXT_DI: U14.6 (OUTD); also elsewhere on the board
/RS485/ISO_DI: F1.1; also elsewhere on the board
/stm32/485_RX: U14.5 (OUTC); also elsewhere on the board
/stm32/485_TX: U14.4 (INB); also elsewhere on the board
/stm32/485_TXEN: U14.3 (INA); also elsewhere on the board
GND: C61.2, C62.2, U14.2 (GND1), U14.8 (GND1); also elsewhere on the board
GNDREF: C63.2, C64.2, C65.2, D5.3 (common), D6.2 (A), U14.9 (GND2), U14.10 (SEL), U14.15 (GND2), U15.5 (GND); also elsewhere on the board
unnamed: D6.1 (K), F1.2, R34.2, R35.1
unnamed: R32.2, U15.7 (B)
unnamed: R33.2, U15.6 (A)
unnamed: R35.2, U14.11 (IND)
unnamed: U14.12 (INC), U15.1 (RO)
unnamed: U14.13 (OUTB), U15.4 (DI)
unnamed: U14.14 (OUTA), U15.2 (~RE), U15.3 (DE)

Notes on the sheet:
0ZCM0002FF2G
SMF3.3
